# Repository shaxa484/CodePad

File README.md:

# CodePad

CodePad is a 6 key macropad with a rotary encoder, and an OLED Display made for helping me while coding. It uses QMK firmware.

## Features:
- Dual layer plastic case. 
- 128x32 OLED Display
- EC11 Rotary encoder for whatever you want(volume control, scrolling)
- 6 Keys

## CAD Model:
Everything fits together using 4 M3 Bolts and heatset inserts. 4 for the each corner of the case. 

It has 2 separate printed pieces. The base where the PCB sits, and the top cover.

Made in Fusion360.

## PCB
Here's my PCB! It was made in KiCad.

Schematic

PCB

I didn't use any matrixes cause easier the better no need to make it complex.

## Firmware Overview
This hackpad uses [QMK](https://qmk.fm/) firmware for everything. 

- the rotary encoder changes volume. press to mute
- The 6 keys currently as copy, paste, shift select, pause and play, keyboard brightness up and down I'm planning to change it later.
- The OLED is would have a clock but I'm searching for more creative ideas for it

## BOM:
Here is everything needed to make this hackpad

- 6x Cherry MX Switches
- 6x DSA Keycaps
- 4x M3x5x4 Heatset inserts
- 4x M3x16mm SHCS Bolts
- 1x 0.91" 128x32 OLED Display
- 1x EC11 Rotary Encoder
- 1x XIAO RP2040
- 1x Case (2 printed parts)

## Extra stuff

Fun fact: I completed building it a day before my 19th birthday

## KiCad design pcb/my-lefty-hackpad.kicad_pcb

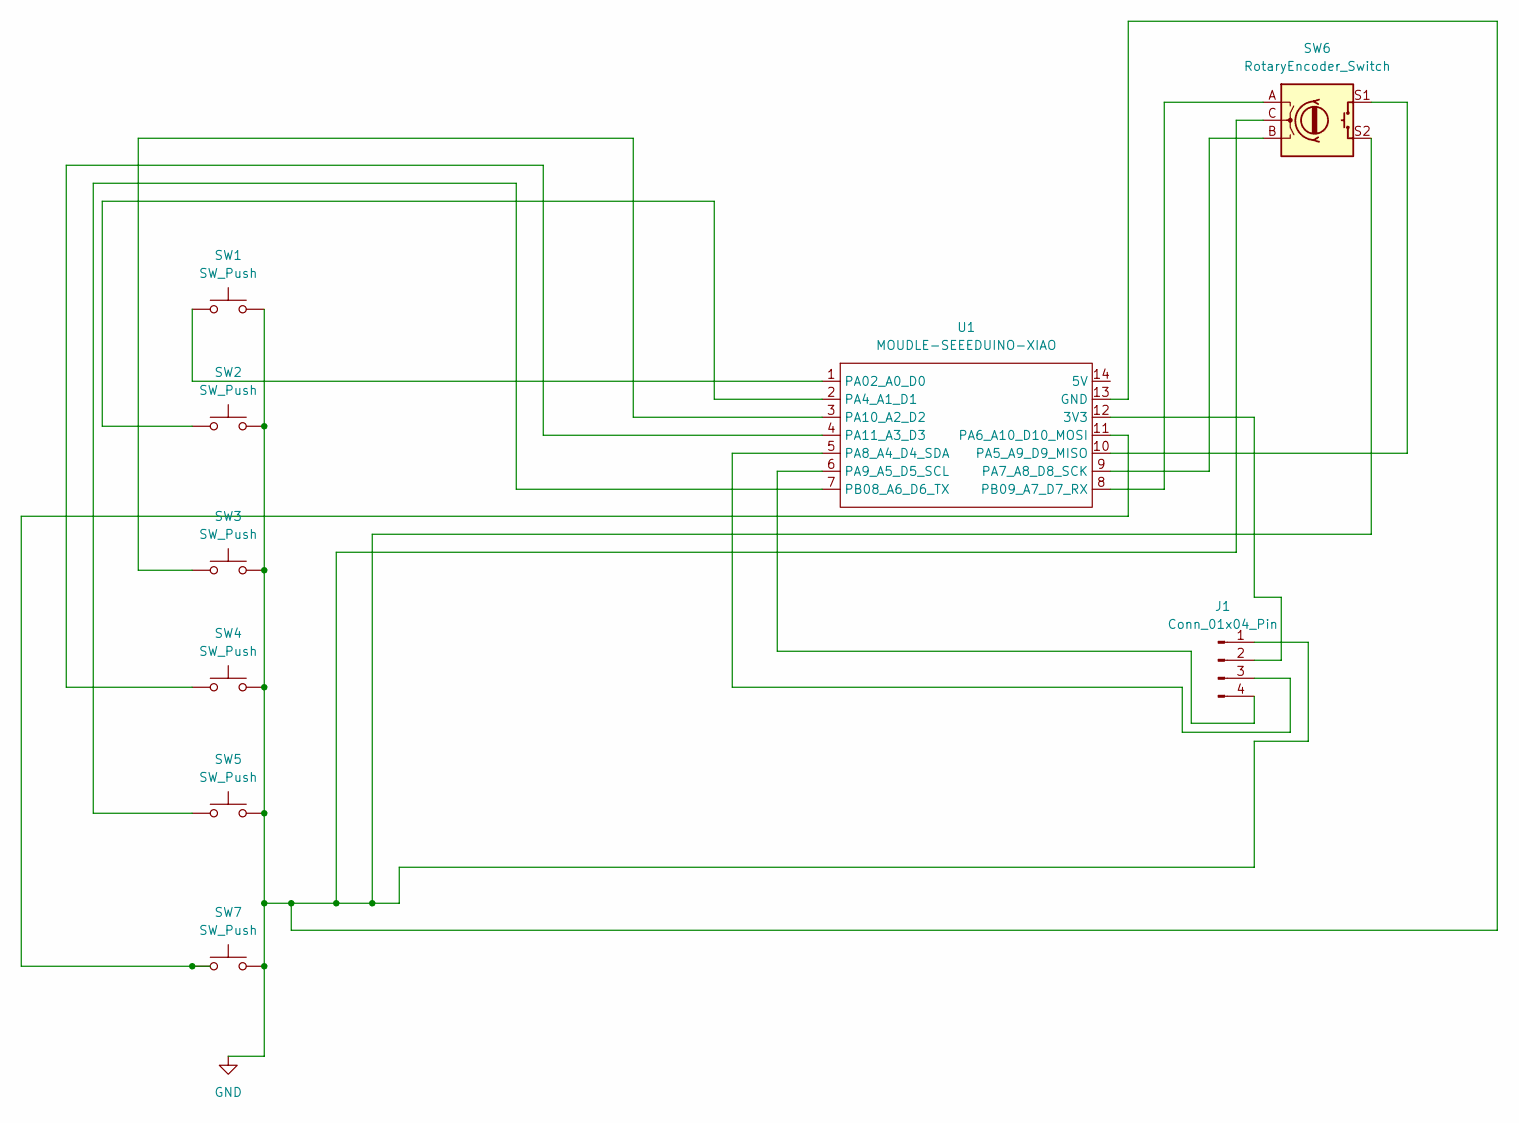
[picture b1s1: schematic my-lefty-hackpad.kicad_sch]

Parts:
J1: Conn_01x04_Pin; PinHeader_1x04_P2.54mm_Vertical
SW1, SW2, SW3, SW4, SW5, SW7: SW_Push; SW_Cherry_MX_1.00u_Plate
SW6: RotaryEncoder_Switch; RotaryEncoder_Alps_EC11E-Switch_Vertical_H20mm
U1: MOUDLE-SEEEDUINO-XIAO; XIAO-Generic-Hybrid-14P-2.54-21X17.8MM

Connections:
GND: J1.1, SW1.2, SW2.2, SW3.2, SW4.2, SW5.2, SW6.C, SW6.S2, SW7.2, U1.13 (GND)
unnamed: J1.2, U1.12 (3V3)
unnamed: J1.3, U1.5 (PA8_A4_D4_SDA)
unnamed: J1.4, U1.6 (PA9_A5_D5_SCL)
unnamed: SW1.1, U1.1 (PA02_A0_D0)
unnamed: SW2.1, U1.2 (PA4_A1_D1)
unnamed: SW6.S1, U1.10 (PA5_A9_D9_MISO)
unnamed: SW7.1, U1.11 (PA6_A10_D10_MOSI)
unnamed: SW6.B, U1.9 (PA7_A8_D8_SCK)
unnamed: SW3.1, U1.3 (PA10_A2_D2)
unnamed: SW4.1, U1.4 (PA11_A3_D3)
unnamed: SW5.1, U1.7 (PB08_A6_D6_TX)
unnamed: SW6.A, U1.8 (PB09_A7_D7_RX)

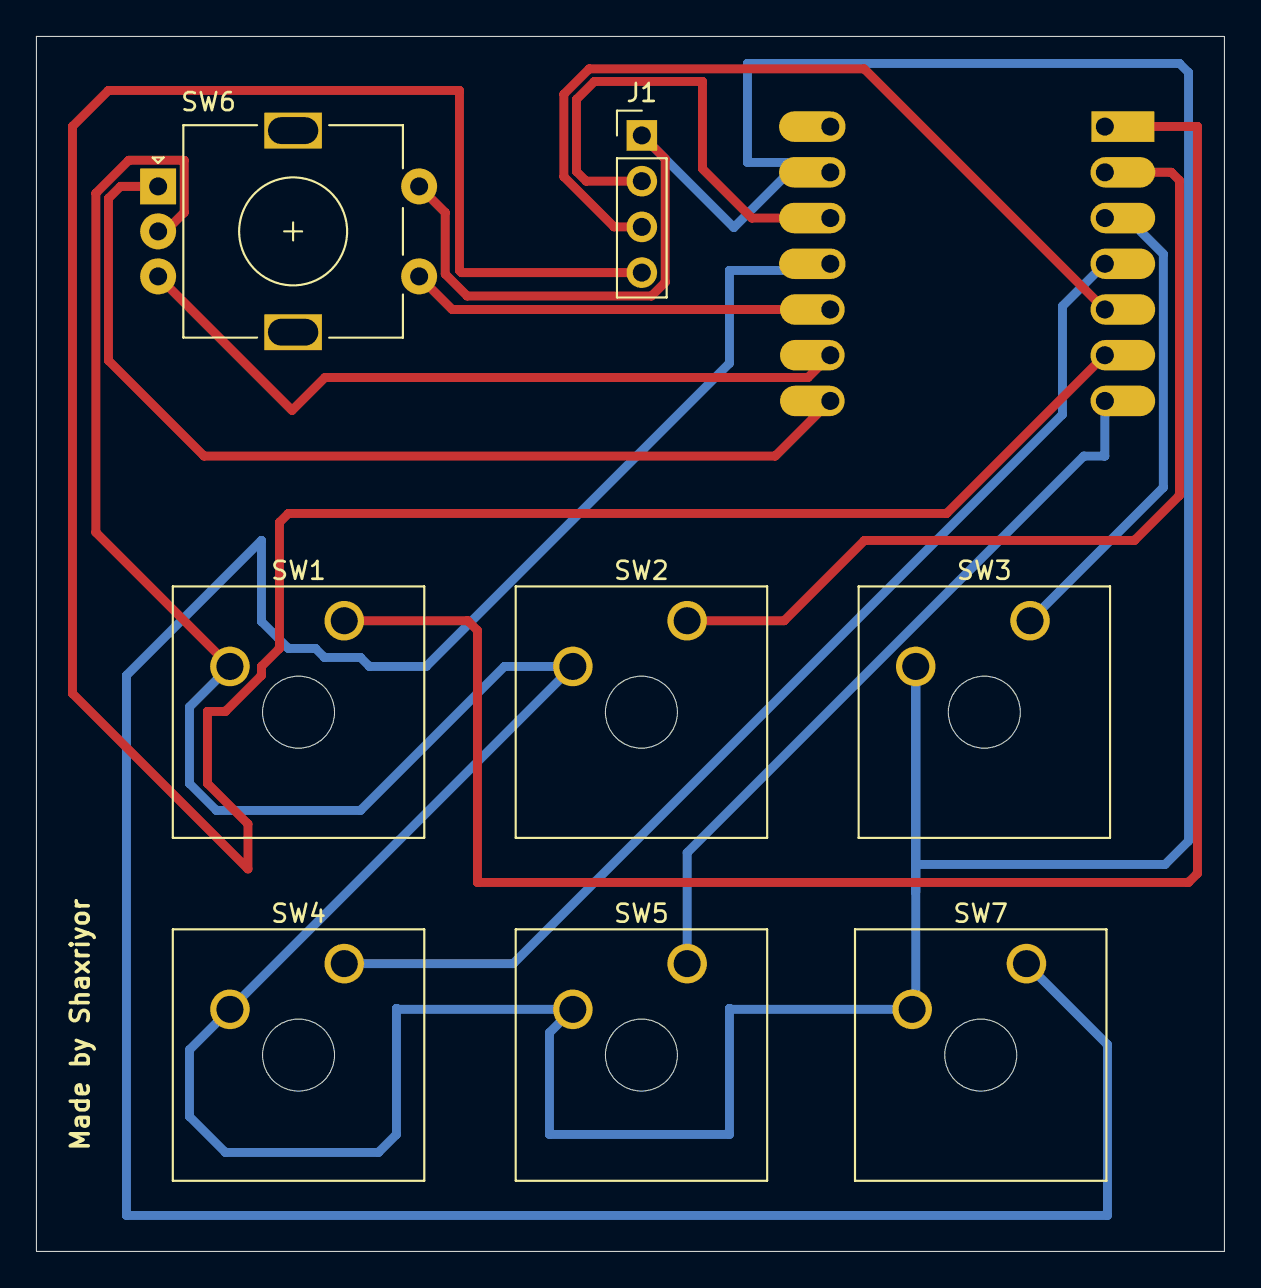
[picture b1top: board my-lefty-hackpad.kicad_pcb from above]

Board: 2 copper layers, 66.0 x 67.5 mm, 9 parts (1 on the bottom side), 13 nets.

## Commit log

2026-06-22 Gerbers files
2026-06-22 pcb and schematic pictures
2026-06-22 Add firmware info.json for CodePad keyboard
2026-06-22 Add initial hardware driver configuration
2026-06-22 Create README.md for CodePad project
    Added detailed README for CodePad project including features, CAD model, PCB details, firmware overview, BOM, and extra information.
2026-06-22 Add configuration definitions for firmware
2026-06-22 Update README
    Removed mention of silkscreen import from Figma.
2026-06-22 update on pcb
2026-06-22 Update info.json to modify features
    Removed diode_direction and added encoder configuration.
2026-06-22 Update configurations
2026-06-22 Implement keymap
2026-06-23 Cleaning the unnecessary
